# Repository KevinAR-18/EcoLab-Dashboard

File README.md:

# EcoLab Dashboard - Smart Laboratory Management System

EcoLab Dashboard - DTEDI Electronics Laboratory Internship 2025 x Final Project  
**Author:** Stephanus Kevin Andika Rata  
**Internship Hardware (Smart AC & Lamp):** Ilham Purnomo

---

## Project Overview

EcoLab Dashboard is a **Smart Laboratory Management System** desktop application built with **PySide6 (Qt)** and **Firebase Authentication** to monitor and control laboratory devices in real time.

The system currently supports:
- **EcoLab Power Monitoring (Growatt)**
- **Smart Socket**
- **Smart Lamp**
- **Smart AC Control**
- **Weather Station Monitoring**
- **Laboratory sensor and device status monitoring**

---

## Main Features

- **Firebase Authentication**: email/password, Google Sign-In, and Guest Mode
- **Role-based Access Control**: guest, user, and admin
- **Session Management**: remember-me support
- **Admin Panel**: laboratory user account management
- **Smart Socket Control**: relay, timer, schedule, and energy monitoring
- **Smart Socket Safety Protection**: load warning, overload popup, and automatic cutoff
- **Smart Socket Power-Off Protection**: admin-configured blocked/password mode with Firebase sync
- **Smart Socket Recording**: store monitoring data in application memory
- **Smart Socket Export**: export per-socket data to CSV
- **Smart Socket Graph**: per-socket monitoring charts inside the control popup
- **EcoLab Power Monitoring**: Growatt inverter monitoring on page 1
- **Weather Station Monitoring**: laboratory weather data monitoring
- **Smart Lamp Control**
- **Smart AC Control**
- **Windows 11 Dark Mode Handling**: light theme enforcement for key widgets

---

## Technology Stack

### Frontend
- **PySide6** (Qt6)
- **Python** 3.10+
- **PySide6.QtCharts** for Smart Socket charts

### Backend / Services
- **Firebase Authentication**
- **Pyrebase4**
- **MQTT** (`paho-mqtt`) for IoT device communication
- **Growatt data integration** for inverter monitoring
- **Weather data integration** for Weather Station monitoring
- **Google Cloud / OAuth config** for Google login

### Hardware
- **Growatt Inverter** for EcoLab Power Monitoring
- **ESP32-C3** for Smart Socket
- **Wemos D1 Mini** for Smart Lamp and Smart AC
- **PZEM-004T v3.0** for Smart Socket energy monitoring
- **DS1302 RTC** for Smart Socket timer and schedule
- **PCB Smart AC & Smart Lamp** designed by **Ilham Purnomo** (KiCad)

---

## Installation

### Prerequisites

```bash
Python 3.10 or higher
```

### Install dependencies

```bash
pip install -r requirements.txt
```

### Runtime configuration

The application needs four external setup areas:

1. Firebase web configuration in `.env`
2. Google OAuth client credential in `credentials/client_secret.json`
3. MQTT TLS certificate in `credentials/ca.crt` or `credentials/ca2.crt`
4. Growatt account credential in `.env`

See [credentials/README.md](credentials/README.md) for the detailed credential guide.

### Firebase setup

1. Create or open the EcoLab project in Firebase Console.
2. Enable Authentication for Email/Password.
3. Enable Google Sign-In in Firebase Authentication if you want Google login.
4. Copy the Firebase web app values into the root `.env` file.
5. Generate a service account key and place it in `credentials/firebase_service_account.json`.

Example Firebase web config values:

```json
{
  "apiKey": "YOUR_API_KEY",
  "authDomain": "YOUR_PROJECT.firebaseapp.com",
  "databaseURL": "https://YOUR_PROJECT.firebaseio.com",
  "projectId": "YOUR_PROJECT_ID",
  "storageBucket": "YOUR_PROJECT.appspot.com",
  "messagingSenderId": "YOUR_SENDER_ID",
  "appId": "YOUR_APP_ID"
}
```

Required `.env` keys:

```env
ECOLAB_FIREBASE_API_KEY=
ECOLAB_FIREBASE_AUTH_DOMAIN=
ECOLAB_FIREBASE_DATABASE_URL=
ECOLAB_FIREBASE_PROJECT_ID=
ECOLAB_FIREBASE_STORAGE_BUCKET=
ECOLAB_FIREBASE_MESSAGING_SENDER_ID=
ECOLAB_FIREBASE_APP_ID=
ECOLAB_FIREBASE_SERVICE_ACCOUNT=
```

Notes:

- Leave `ECOLAB_FIREBASE_SERVICE_ACCOUNT` empty if you use `credentials/firebase_service_account.json`.
- Fill `ECOLAB_FIREBASE_SERVICE_ACCOUNT` only if the service account file is stored somewhere else.

### Google OAuth setup

Google Sign-In does not use only Firebase settings. It also needs a Google OAuth client JSON file.

Prepare:

- `credentials/client_secret.json`

Steps:

1. Open Google Cloud Console.
2. Select the same Google Cloud project linked to EcoLab.
3. Go to `APIs & Services` -> `Credentials`.
4. Create or open the OAuth client used by the app.
5. Download the client JSON.
6. Rename it to `client_secret.json`.
7. Place it inside the `credentials/` folder.

If Google Sign-In fails, the first thing to verify is whether `credentials/client_secret.json` matches the active Google Cloud project.

### MQTT TLS setup

MQTT communication for the IoT devices uses TLS and requires a CA certificate file.

Prepare:

- `credentials/ca.crt` as the default CA certificate
- `credentials/ca2.crt` as an optional backup CA certificate for some simulator or broker setups

Required `.env` keys:

```env
ECOLAB_MQTT_BROKER=
ECOLAB_MQTT_PORT=8883
ECOLAB_MQTT_USERNAME=
ECOLAB_MQTT_PASSWORD=
ECOLAB_MQTT_CA_CERT=credentials/ca.crt
ECOLAB_MQTT_USE_TLS=true
```

What to prepare for MQTT TLS:

1. MQTT broker hostname or IP
2. MQTT username and password
3. TLS-enabled MQTT port, usually `8883`
4. CA certificate file, usually `credentials/ca.crt`
5. Fallback CA certificate if your simulator or broker setup uses `ca2.crt`

Notes:

- `main.py` defaults to `credentials/ca.crt` when `ECOLAB_MQTT_CA_CERT` is not overridden.
- Some simulator files in `hardware_TA/` still point to `ca2.crt`, so keep both certificate files available unless you are standardizing them.
- Do not embed certificate contents directly into the firmware.

### Growatt setup

Dashboard startup currently initializes the Growatt panel during `MainWindow` creation, so these `.env` keys are required when opening the dashboard:

```env
ECOLAB_GROWATT_USERNAME=
ECOLAB_GROWATT_PASSWORD=
```

Notes:

- Use the same Growatt account that has access to the target storage/inverter plant.
- If the account has no accessible plant or storage device, the Growatt panel will fail during startup.

### Minimum files checklist

Before running the app, make sure these files exist:

```text
.env
credentials/client_secret.json
credentials/firebase_service_account.json
credentials/ca.crt
```

Optional but recommended:

```text
credentials/ca2.crt
```

Minimum required `.env` groups for a full dashboard launch:

- Firebase web config keys
- MQTT connection keys
- Growatt account keys

---

## Usage

### Run the application

```bash
python launcher.py
```

### Authentication options

1. **Email Login**  
   Sign in with email and password.
2. **Google Sign-In**  
   Sign in with a Google account.
3. **Guest Mode**  
   Read-only access without device control.

### User roles

| Role | Access |
|------|--------|
| **Guest** | Monitoring only, without device control |
| **User** | Device control and main dashboard access |
| **Admin** | All user features plus the admin panel |

---

## Smart Socket Updates

The current Smart Socket feature set includes:

- Per-socket relay ON/OFF control
- Per-socket timer
- Start/stop schedules with **daily** and **onetime** modes
- Monitoring for **Voltage, Current, Power, Energy, Frequency, PF**
- Control popup with **Control**, **Data**, **Graph**, **Warning**, and **Setting** tabs
- Per-socket monitoring data recording
- Configurable recording interval from the popup
- **Follow Schedule** option to automatically start recording when a schedule becomes active
- **Autosave CSV** when schedule-based recording ends
- Load warning levels for **elevated**, **high**, and **critical** current
- Light warning popup for elevated load with cooldown control
- Critical overload protection with user response popup, grace period, and automatic relay cutoff
- Automatic schedule clearing before forced OFF when overload protection is triggered during an active schedule
- Admin-only Smart Socket **Setting** tab inside the popup to configure power-off protection per socket
- Power-off protection modes: **Blocked** and **Password required**
- Protection configuration stored in **Firebase Realtime Database** so it can be shared across multiple PCs
- Per-socket CSV export
- Per-socket charts with selectable metrics
- Table and chart refresh only while recording is active

Implementation notes:
- The Python Smart Socket simulator has been aligned with the latest firmware concept.
- Firmware files from `smartsocket2.ino` to `smartsocket5.ino` were derived from `smartsocket.ino` with adjusted MQTT topics.

---

## Project Structure

The current project structure after refactoring is:

```text
Aplikasi EcoLab -  New/
|-- launcher.py
|-- loginmain.py
|-- main.py
|-- create_admin.py
|-- README.md
|-- requirements.txt
|-- build.bat
|-- .env.example
|-- auth/
|   |-- auth_service.py
|   `-- session_manager.py
|-- config/
|   |-- firebase_settings.py
|   |-- login_settings.py
|   `-- path_utils.py
|-- dialogs/
|   |-- admin_window.py
|   `-- smartsocket_popup.py
|-- services/
|   |-- smartsocket_recorder.py
|   |-- smartsocket_protection_store.py
|   `-- smartsocket_settings_manager.py
|-- app/
|   `-- setup/
|       |-- ac_setup.py
|       |-- arrow_setup.py
|       |-- lamp_setup.py
|       |-- smartsocket_setup.py
|       `-- switch_setup.py
|-- backend/
|   |-- mqtt_client.py
|   |-- mqtt_dht22_backend.py
|   |-- mcu_status_backend.py
|   |-- smartsocket_backend.py
|   |-- lampbutton_backend.py
|   |-- acbutton_backend.py
|   |-- growatt_backend.py
|   |-- growatt_worker.py
|   `-- weathercloud_backend.py
|-- widgets/
|   |-- ac_button.py
|   |-- flow_arrow.py
|   |-- lamp_button.py
|   `-- switch_button.py
|-- ui/
|   |   (Qt Designer .ui source files)
|   |-- ui_functions.py
|   |-- ui_theme_helper.py
|   |-- ui_loginpage.py
|   |-- ui_mainwindow.py
|   |-- ui_adminpanel.py
|   |-- ui_role_selection.py
|   `-- ui_smartsocket_popup.py
|-- credentials/
|-- icon/
|-- images/
|-- hardware_TA/
|   `-- PCB Designs/            (KiCad PCB layouts by Ilham Purnomo)
`-- resources_rc.py
```

---

## Architecture Overview

### Entry Flow

- `launcher.py` is the main application entry point.
- It loads any saved session through `auth/session_manager.py`.
- If a valid session exists, it opens the main dashboard.
- Otherwise, it opens `loginmain.py`.

### Authentication Layer

- `auth/auth_service.py` handles Firebase authentication and user records.
- `auth/session_manager.py` stores the local session file used by remember-me behavior.
- `create_admin.py` is a helper script for manually creating the first admin account.

### Main Application Layer

- `main.py` contains the main dashboard window and top-level application orchestration.
- `loginmain.py` handles login, sign-up, forgot password, guest mode, and the admin/dashboard selection flow.
- `dialogs/admin_window.py` contains the admin panel.
- `dialogs/smartsocket_popup.py` contains the detailed Smart Socket control and monitoring popup.
- `services/smartsocket_protection_store.py` stores Smart Socket power-off protection data in Firebase Realtime Database.

### Setup Helpers

The `app/setup/` modules are thin UI wiring helpers:

- `lamp_setup.py` creates and connects custom lamp buttons
- `switch_setup.py` creates and connects Smart Socket switch buttons
- `ac_setup.py` creates and connects the custom AC button
- `arrow_setup.py` creates and stores flow arrows
- `smartsocket_setup.py` connects Smart Socket backend signals to the main window

### Backend Layer

The `backend/` folder contains service and integration modules:

- `mqtt_client.py` manages the shared MQTT connection
- `mqtt_dht22_backend.py` stores and filters DHT22 sensor messages
- `mcu_status_backend.py` tracks MCU online/offline state
- `smartsocket_backend.py` handles MQTT topics for all Smart Socket devices
- `lampbutton_backend.py` and `acbutton_backend.py` send control commands
- `growatt_backend.py` fetches inverter data
- `growatt_worker.py` runs Growatt fetches outside the UI thread
- `weathercloud_backend.py` fetches weather station data

### UI and Widget Layer

- `ui/` contains helper code and generated Python modules from Qt Designer `.ui` files
- `widgets/` contains handwritten custom widgets used by the dashboard
- `resources_rc.py` contains the compiled Qt resource bindings

---

## Hardware TA

The `hardware_TA/` folder contains firmware and simulators used for development and device integration testing.

### Arduino / firmware

1. **smartsocket.ino** - Smart Socket 1 firmware based on MQTT
2. **smartsocket2.ino** - Smart Socket 2 firmware based on MQTT
3. **smartsocket3.ino** - Smart Socket 3 firmware based on MQTT
4. **smartsocket4.ino** - Smart Socket 4 firmware based on MQTT
5. **smartsocket5.ino** - Smart Socket 5 firmware based on MQTT
6. **smartlampcontrol.ino** - Smart Lamp firmware
7. **smartaccontrol.ino** - Smart AC Control firmware

### Python simulators

1. **smartsocket_simulator.py** - Smart Socket 1 simulator
2. **smartsocket2_simulator.py** - Smart Socket 2 simulator
3. **smartsocket3_simulator.py** - Smart Socket 3 simulator
4. **smartsocket4_simulator.py** - Smart Socket 4 simulator
5. **smartsocket5_simulator.py** - Smart Socket 5 simulator
6. **mcua_simulator.py** - MCU-A simulator
7. **mcub_simulator.py** - MCU-B simulator

### Example: run a simulator

```bash
cd hardware_TA
python smartsocket_simulator.py
```

### PCB Designs (KiCad)

- **Smart AC & Smart Lamp** — PCB designed by **Ilham Purnomo** during the 2025 internship.

| PCB | Designer | Location | Description |
|-----|----------|----------|-------------|
| **PCB Smart AC** | Ilham Purnomo | `hardware_TA/PCB Designs/Rangkaian Control AC/PCB AC/` | AC control relay, transformer, and XL6009 DC-DC converter |
| **PCB Smart Lamp** | Ilham Purnomo | `hardware_TA/PCB Designs/Rangkaian Control Lampu/PCB_LAMPU/` | Lamp control relay, transformer, and XL6009 DC-DC converter |

Custom KiCad libraries are located under `Libraries for Arduino IDE/` in each project folder.

---

## Feature Details

### Session management

- Save login sessions
- Remember-me support
- Auto-login when the session is still valid
- Application logout

### Admin panel

- View user list
- Approve accounts
- Update user/admin roles
- Block/unblock accounts
- Update passwords for non-Google users
- Delete accounts

### Smart Socket

- Device status monitoring
- Relay control
- Countdown timer
- Automatic scheduling
- Real-time energy monitoring
- Multi-level current warning system
- Automatic overload cutoff for critical current conditions
- Admin-only power-off protection settings inside the Smart Socket popup
- Power-off protection synced through Firebase so the same socket rules can be read from different PCs
- Data recording, CSV export, and charts
- **Final Project** — fully developed by **Stephanus Kevin Andika Rata** (Hardware & Software)

### Smart Lamp

- Laboratory lamp control
- MQTT-based switching
- Supports multiple lamp channels in the control room page
- Developed together with **Ilham Purnomo**
- Hardware PCB design: **Ilham Purnomo**

### Smart AC

- IR-based AC control
- Cooling and fan modes
- Temperature settings
- Developed together with **Ilham Purnomo**
- Hardware PCB design: **Ilham Purnomo**

### EcoLab Power Monitoring

- Displays **Growatt inverter** data on page 1
- EcoLab power summary and live monitoring
- Serves as the main laboratory energy monitoring page

### Weather Station Monitoring

- Displays laboratory weather station data
- Environmental sensor monitoring on the dashboard
- Integrated into the monitoring page for surrounding condition tracking

---

## Authentication Flow

```text
launcher.py -> check session
  |- valid session -> open dashboard
  |- no session -> open login window
       |- email/password -> Firebase -> save session -> dashboard
       |- Google sign-in -> OAuth -> save session -> dashboard
       |- guest mode -> temp session -> dashboard (limited)
```

---

## Notes

- Use `launcher.py` as the main application entry point.
- The local session file is created automatically after a successful login.
- Firebase credential files are not included in the repository.
- Several key widgets are forced into a light theme to avoid text color issues on Windows 11 dark mode.
- Smart Socket MQTT firmware no longer stores the CA certificate contents directly inside the `.ino` files.

---

## Contact

**Stephanus Kevin Andika Rata**  
Software Development & System Integration  
DTEDI Electronics Laboratory Internship 2025  
Final Project - EcoLab Smart Laboratory  
DTEDI Electronics Laboratory  
Universitas Gadjah Mada

Email: [kevinandika18@gmail.com](mailto:kevinandika18@gmail.com)

**Ilham Purnomo**  
Hardware PCB Design (Smart AC & Smart Lamp)  
DTEDI Electronics Laboratory Internship 2025  
DTEDI Electronics Laboratory  
Universitas Gadjah Mada

---

## License & Copyright

Copyright (c) 2026 **Stephanus Kevin Andika Rata**  
PCB Design (Smart AC & Lamp): **Ilham Purnomo**

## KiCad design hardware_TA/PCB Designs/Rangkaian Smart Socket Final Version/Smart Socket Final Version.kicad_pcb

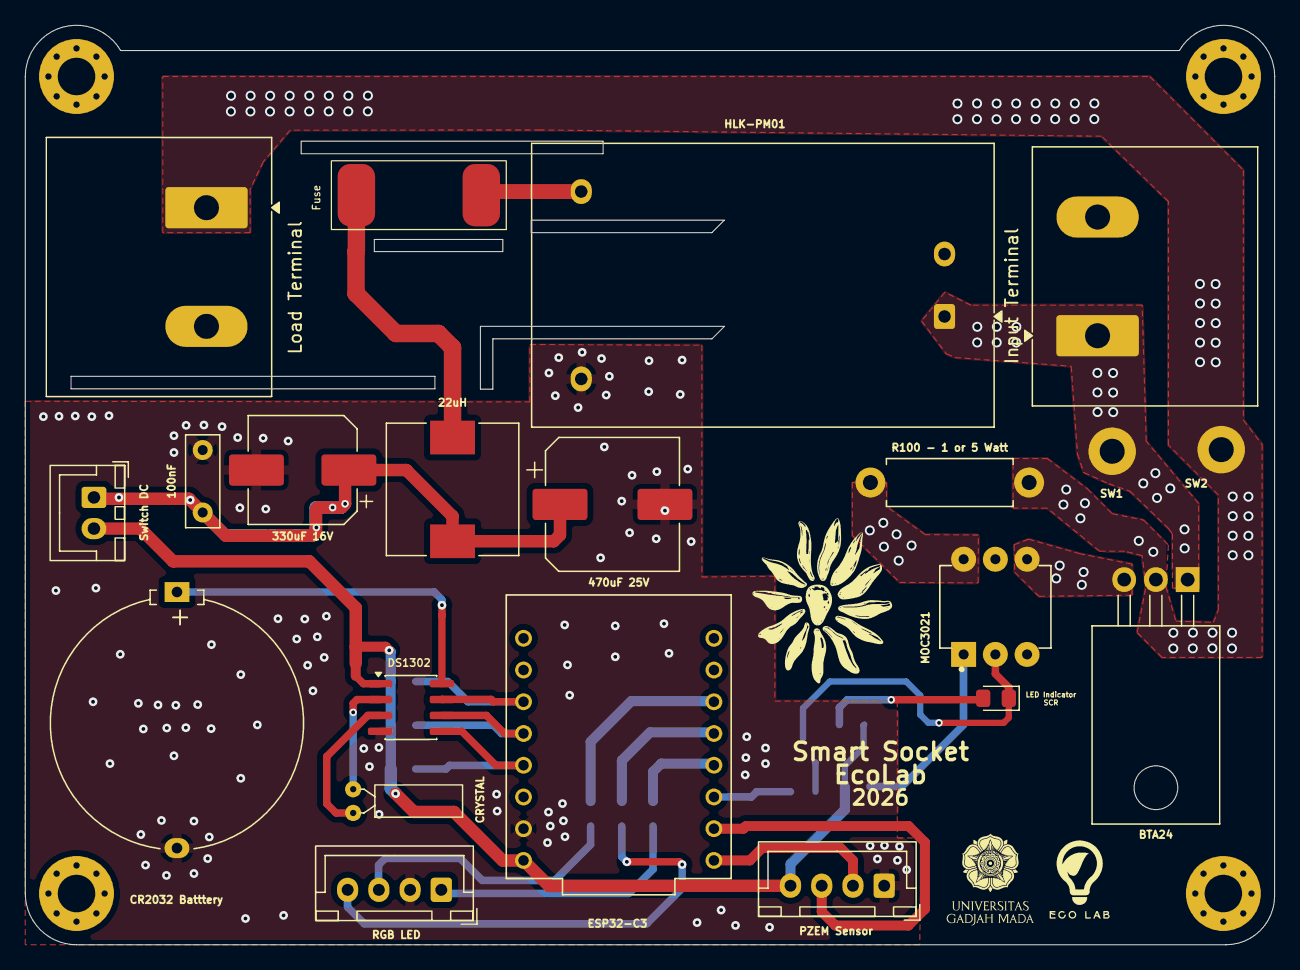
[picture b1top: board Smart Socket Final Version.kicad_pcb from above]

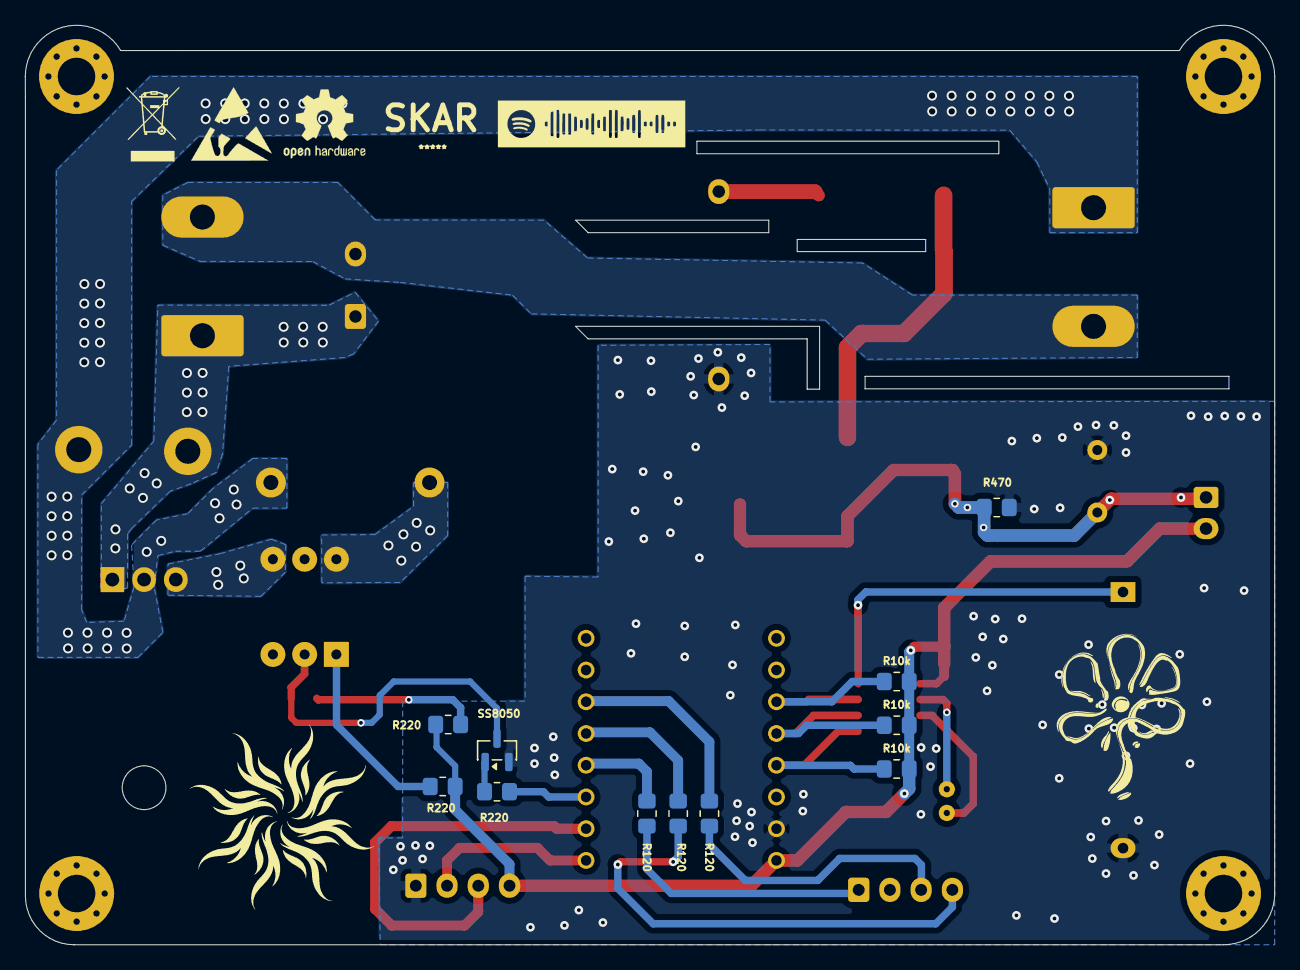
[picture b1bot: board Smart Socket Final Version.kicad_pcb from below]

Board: 2 copper layers, 100.0 x 73.6 mm, 36 parts (11 on the bottom side), 29 nets.

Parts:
22uH: 33uH; L_10.4x10.4_H4.8
100nF: 100nF; C_Rect_L7.2mm_W2.5mm_P5.00mm_FKS2_FKP2_MKS2_MKP2
330uF 16V: 330uF; CP_Elec_8x10.5
470uF 25V: 470uF; CP_Elec_10x10.5
BTA24: BT136-600; TO-220-3_Horizontal_TabDown
CR2032 Batttery: Battery_Cell; Battery_Panasonic_CR2032-HFN_Horizontal_CircularHoles
CRYSTAL: 32.768; Crystal_C26-LF_D2.1mm_L6.5mm_Horizontal
D1: LED; LED_0805_2012Metric_Pad1.15x1.40mm_HandSolder
DS1302: DS1302+; SOIC-8_3.9x4.9mm_P1.27mm
ESP32-C3: ESP32-C3; MODULE_ESP32-C3_SUPERMINI_TH
Fuse: Fuse; Fuse_1808
H3, H4, H5, H6: MountingHole; MountingHole_3mm_Pad_Via
HLK-PM01 : HLK-PM01; Converter_ACDC_Hi-Link_HLK-PMxx
Input Terminal: Input 220V; TerminalBlock_Ningbo-Kagnex_HB9500_1x02_P9.5mm
Load Terminal: AC Socket Load; TerminalBlock_Ningbo-Kagnex_HB9500_1x02_P9.5mm
MOC3021: MOC3021
PZEM Sensor: PZEM Sensor; JST_XH_B4B-XH-A_1x04_P2.50mm_Vertical
R10k, R10k#2, R10k#3: 10k; R_0805_2012Metric_Pad1.20x1.40mm_HandSolder
R100 - 1 or 5 Watt: 100; R_Axial_DIN0411_L9.9mm_D3.6mm_P12.70mm_Horizontal
R120, R120#2, R120#3: 120; R_0805_2012Metric_Pad1.20x1.40mm_HandSolder
R220, R220#2, R220#3: 220; R_0805_2012Metric_Pad1.20x1.40mm_HandSolder
R470: 470; R_0805_2012Metric_Pad1.20x1.40mm_HandSolder
RGB LED: RGB LED; JST_XH_B4B-XH-A_1x04_P2.50mm_Vertical
SS8050: SS8050; SOT-23
SW1: SWITCH FASA IN; MountingHole_2.2mm_M2_DIN965_Pad
SW2: SWITCH FASA to LOAD; MountingHole_2.2mm_M2_DIN965_Pad
Switch DC: DC SWITCH; JST_XH_B2B-XH-A_1x02_P2.50mm_Vertical

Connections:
5V: DS1302.1 (VCC2), ESP32-C3.5V, PZEM Sensor.4, R10k.2, R10k#2.2, R10k#3.2, R220.2, R220#2.2, Switch DC.2
5V Filtered: 22uH.2, 100nF.1, 330uF 16V.1, 470uF 25V.1, R470.2, Switch DC.1
/Fasa to MOC: MOC3021.6, R100 - 1 or 5 Watt.1
/Gate: BTA24.3 (G), MOC3021.4
/VCC1: CR2032 Batttery.1 (+), DS1302.8 (VCC1)
/X1: CRYSTAL.2, DS1302.2 (X1)
/X2: CRYSTAL.1, DS1302.3 (X2)
BLUE LED: ESP32-C3.10 (GPIO10), R120#3.1
CE RTC: DS1302.5 (CE), ESP32-C3.4 (GPIO4), R10k.1
FASA IN: BTA24.1 (A1), HLK-PM01.1 (AC/L), Input Terminal.1, SW1.1
FASA to LOAD: BTA24.2 (A2), Load Terminal.1, R100 - 1 or 5 Watt.2, SW2.1
GND: 100nF.2, 330uF 16V.2, 470uF 25V.2, CR2032 Batttery.2 (-), DS1302.4 (GND), ESP32-C3.G (GND), HLK-PM01.3 (-Vout), PZEM Sensor.1, R470.1, RGB LED.2, SS8050.2 (E)
GREEN LED: ESP32-C3.9 (GPIO9), R120#2.1
IO RTC: DS1302.6 (I/O), ESP32-C3.3 (GPIO3), R10k#3.1
NETRAL: HLK-PM01.2 (AC/N), Input Terminal.2, Load Terminal.2
unnamed: D1.2 (A), R220#2.1
unnamed: D1.1 (K), MOC3021.2, SS8050.3 (C)
unnamed: 22uH.1, Fuse.2
unnamed: R120.2, RGB LED.1
unnamed: R120#3.2, RGB LED.3
unnamed: R120#2.2, RGB LED.4
unnamed: Fuse.1, HLK-PM01.4 (+Vout)
unnamed: R220#3.2, SS8050.1 (B)
unnamed: MOC3021.1, R220.1
RED LED: ESP32-C3.8 (GPIO8), R120.1
RX PZEM: ESP32-C3.6 (GPIO6), PZEM Sensor.3
SCLK RTC: DS1302.7 (SCLK), ESP32-C3.2 (GPIO2), R10k#2.1
TX PZEM: ESP32-C3.5 (GPIO5), PZEM Sensor.2
Trigger SSR: ESP32-C3.7 (GPIO7), R220#3.1

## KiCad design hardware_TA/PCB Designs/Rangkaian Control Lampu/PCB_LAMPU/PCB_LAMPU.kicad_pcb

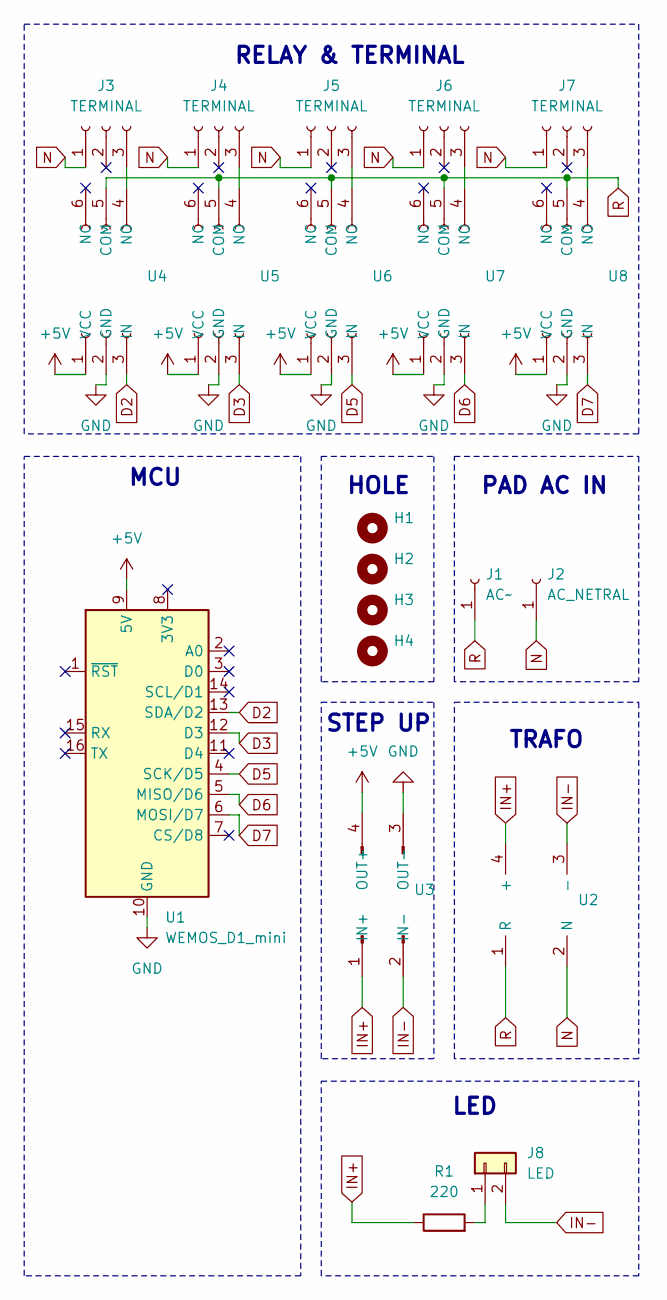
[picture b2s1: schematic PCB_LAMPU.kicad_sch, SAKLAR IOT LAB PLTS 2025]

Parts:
H1, H2, H3, H4: MountingHole; MountingHole_3.2mm_M3_DIN965_Pad
J1: AC~; TestPoint_Pad_4.0x4.0mm
J2: AC_NETRAL; TestPoint_Pad_4.0x4.0mm
J3, J4, J5, J6, J7: TERMINAL; TerminalBlock_MaiXu_MX126-5.0-03P_1x03_P5.00mm
J8: LED; JST_XH_B2B-XH-A_1x02_P2.50mm_Vertical
R1: 220; R_0805_2012Metric
U1: WEMOS_D1_mini; WEMOS_D1_mini_light
U2: TRAFOV1
U3: XL6009_MOD
U4, U5, U6, U7, U8: RELAY_SRD5VDC

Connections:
+5V: U1.9 (5V), U3.4 (OUT+), U4.1 (VCC), U5.1 (VCC), U6.1 (VCC), U7.1 (VCC), U8.1 (VCC)
D2: U1.13 (SDA/D2), U4.3 (IN)
D3: U1.12 (D3), U5.3 (IN)
D5: U1.4 (SCK/D5), U6.3 (IN)
D6: U1.5 (MISO/D6), U7.3 (IN)
D7: U1.6 (MOSI/D7), U8.3 (IN)
GND: U1.10 (GND), U3.3 (OUT-), U4.2 (GND), U5.2 (GND), U6.2 (GND), U7.2 (GND), U8.2 (GND)
IN+: R1.1, U2.4 (+), U3.1 (IN+)
IN-: J8.2, U2.3 (-), U3.2 (IN-)
N: J2.1, J3.1, J4.1, J5.1, J6.1, J7.1, U2.2 (N)
unnamed: J3.3, U4.4 (NO)
unnamed: J4.3, U5.4 (NO)
unnamed: J5.3, U6.4 (NO)
unnamed: J6.3, U7.4 (NO)
unnamed: J7.3, U8.4 (NO)
unnamed: J8.1, R1.2
R: J1.1, U2.1 (R), U4.5 (COM), U5.5 (COM), U6.5 (COM), U7.5 (COM), U8.5 (COM)

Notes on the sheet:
HOLE
PAD AC IN
STEP UP
RELAY & TERMINAL
MCU
LED
TRAFO

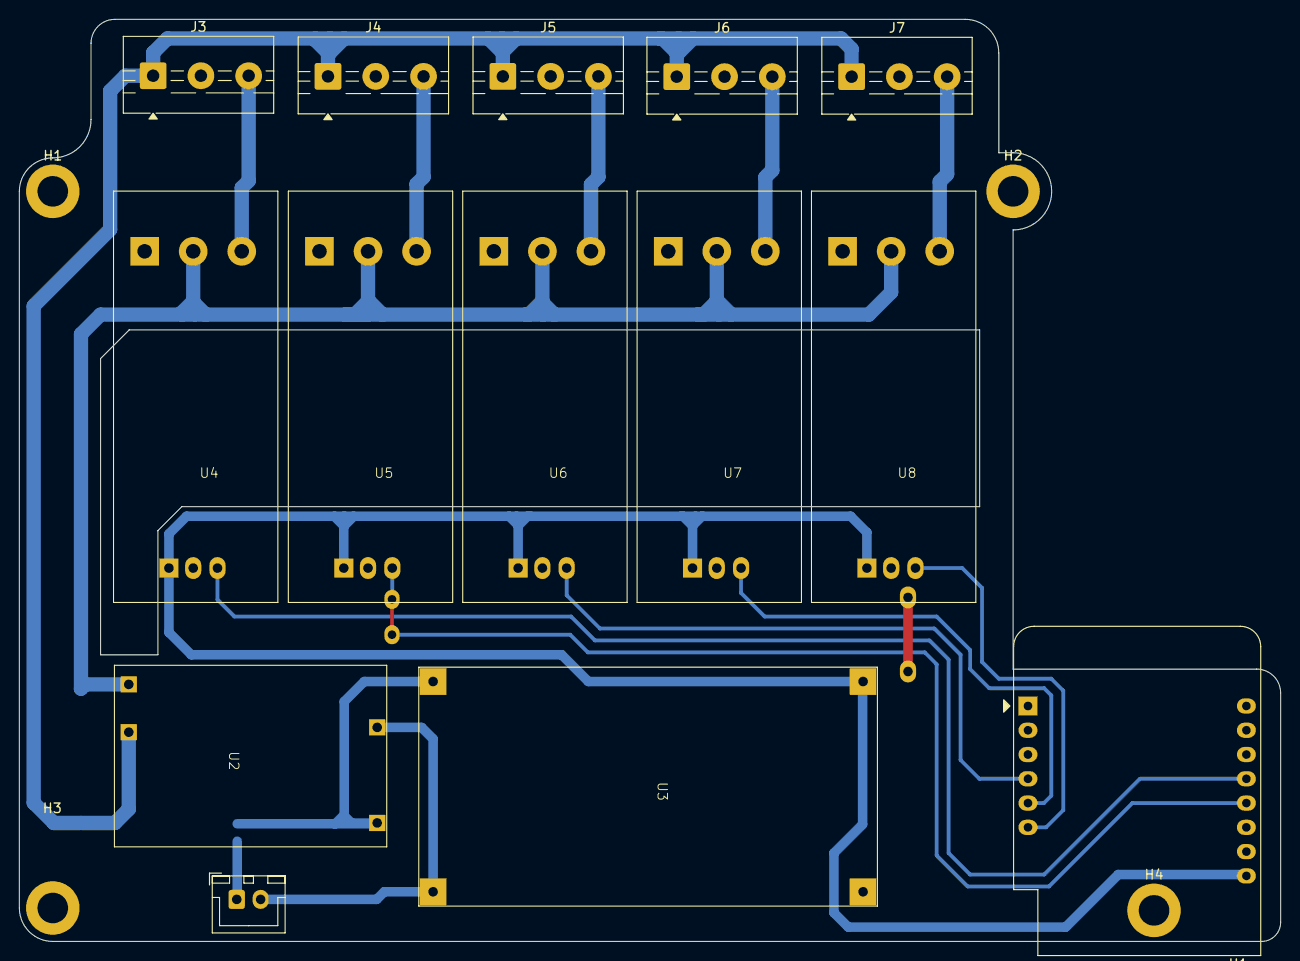
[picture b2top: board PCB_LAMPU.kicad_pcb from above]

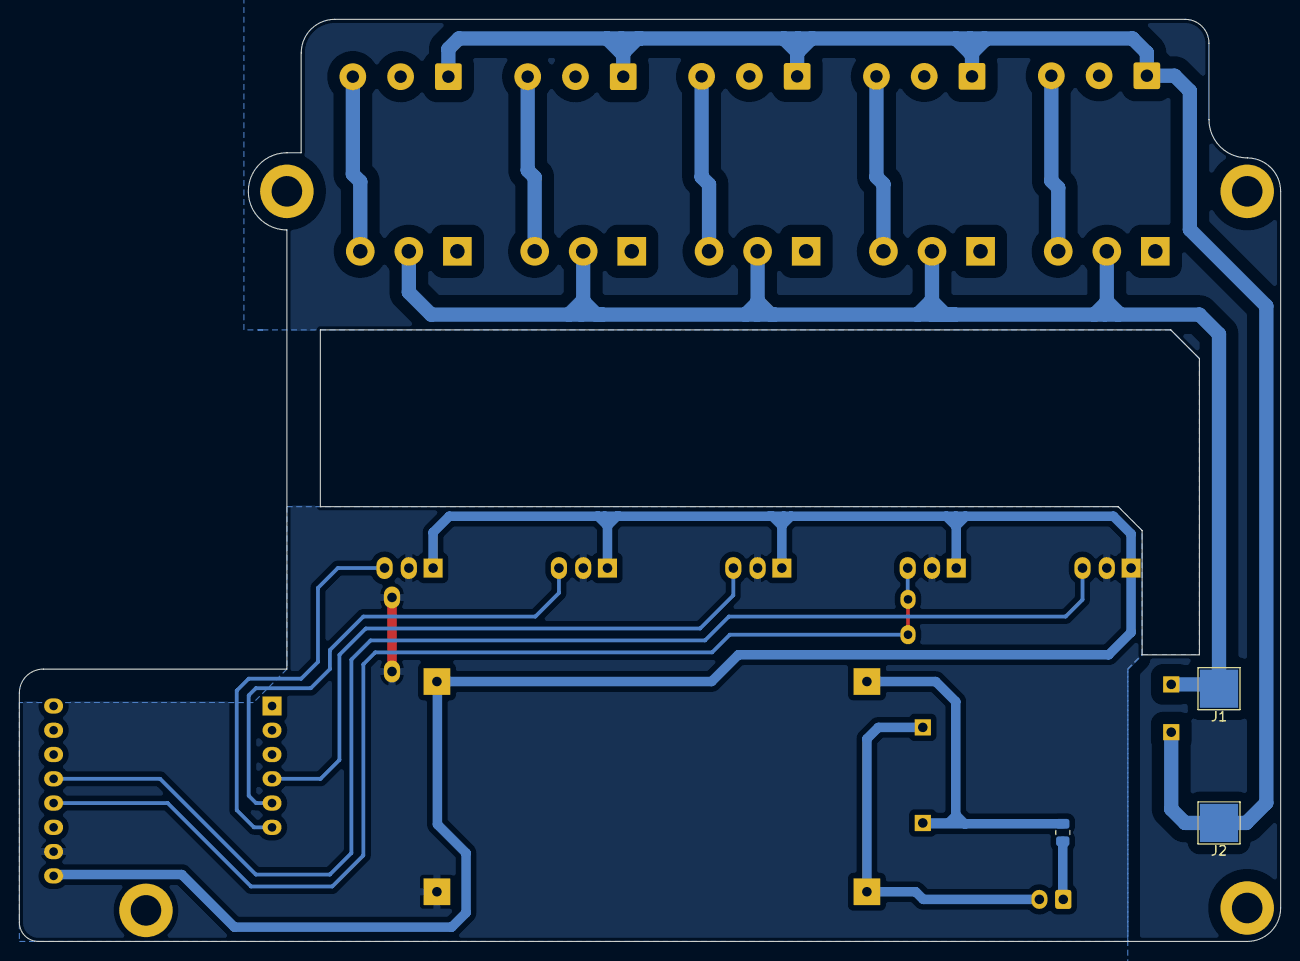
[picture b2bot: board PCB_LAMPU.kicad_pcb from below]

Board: 2 copper layers, 132.0 x 96.5 mm, 21 parts (3 on the bottom side), 17 nets.

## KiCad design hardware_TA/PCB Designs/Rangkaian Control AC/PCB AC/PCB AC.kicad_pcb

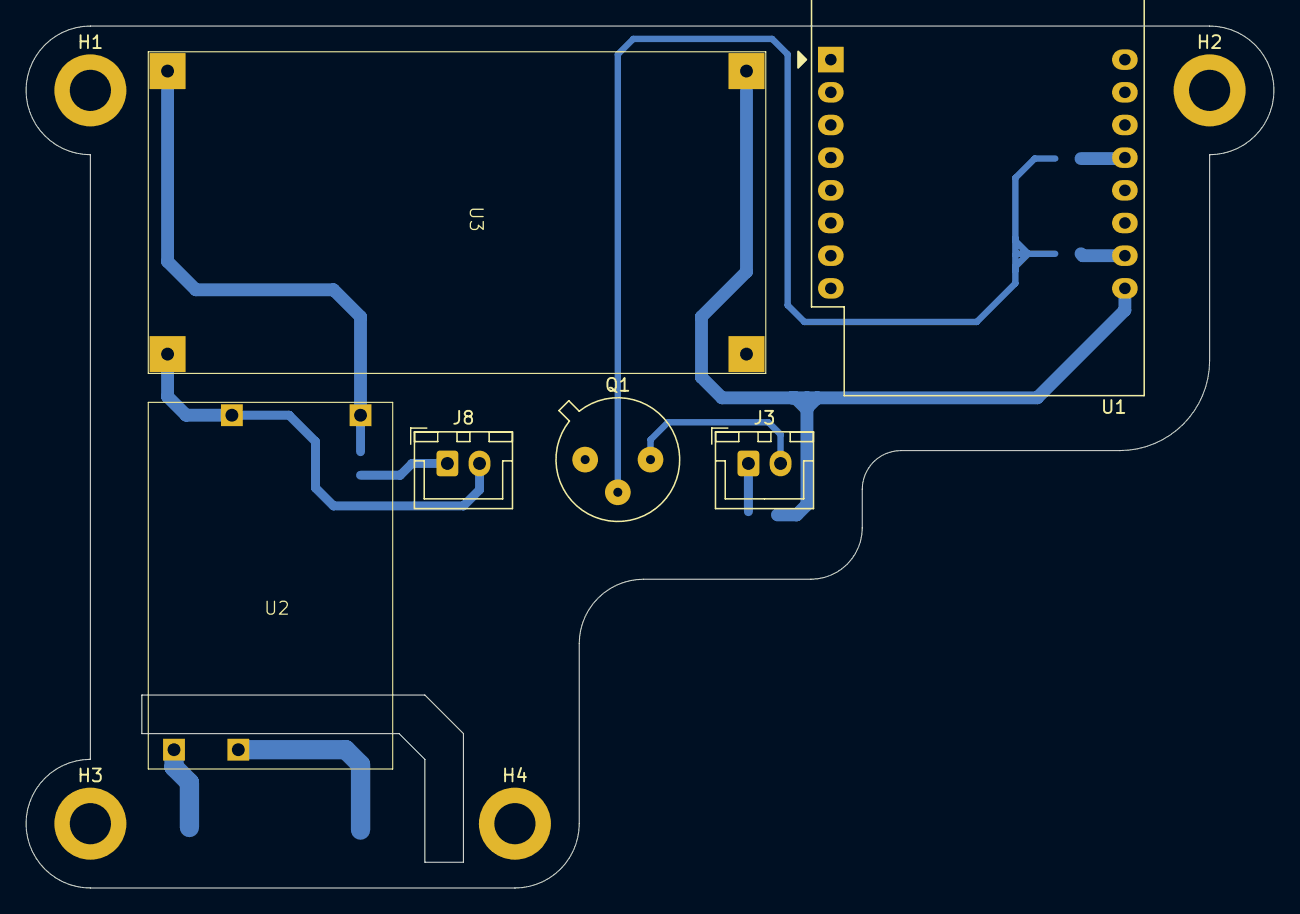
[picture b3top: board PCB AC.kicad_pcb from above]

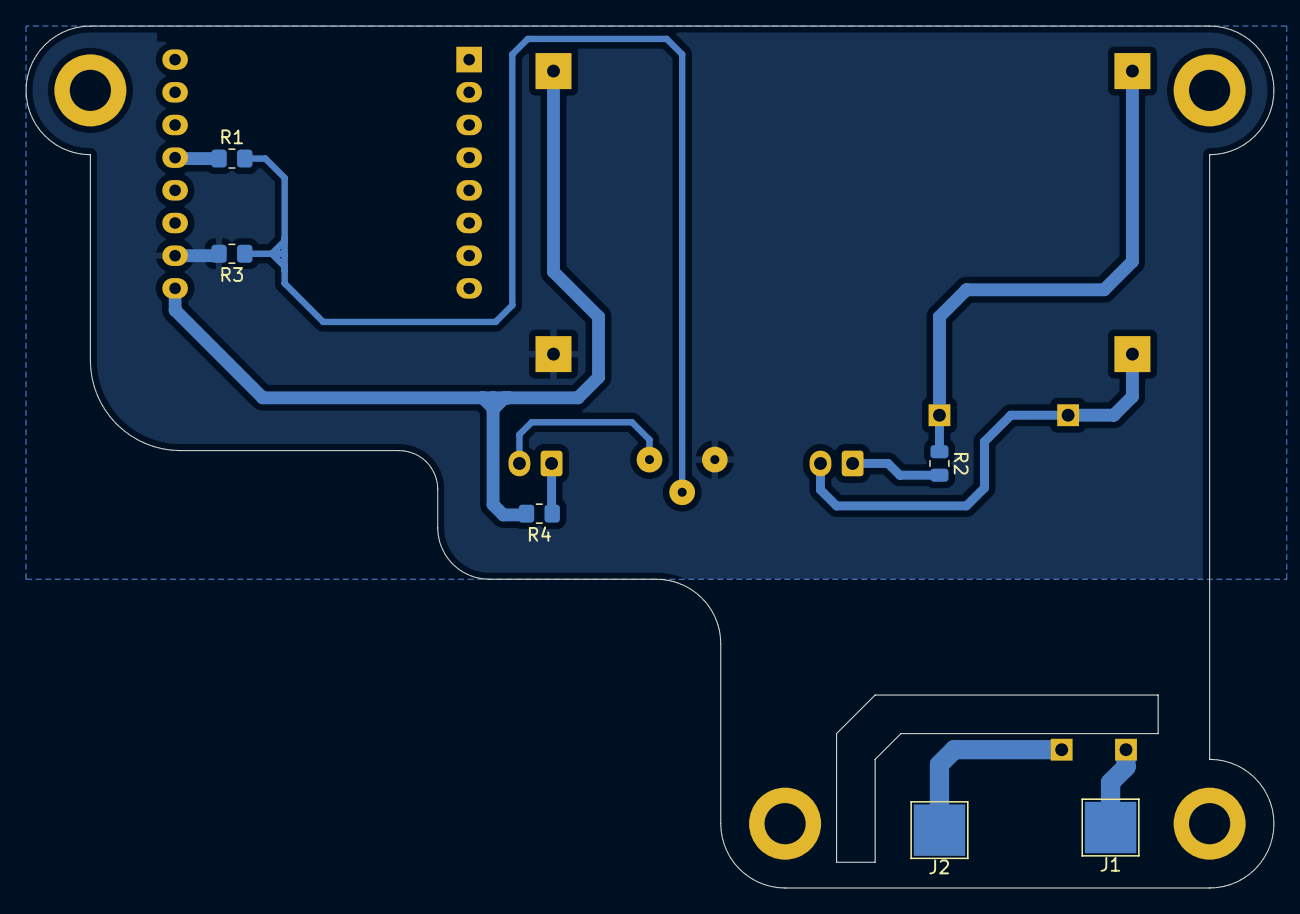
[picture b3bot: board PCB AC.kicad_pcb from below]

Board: 2 copper layers, 97.0 x 67.0 mm, 16 parts (6 on the bottom side), 11 nets.

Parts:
H1, H2, H3, H4: MountingHole; MountingHole_3.2mm_M3_DIN965_Pad
J1: AC~; TestPoint_Pad_4.0x4.0mm
J2: AC_NETRAL; TestPoint_Pad_4.0x4.0mm
J3: IR; JST_XH_B2B-XH-A_1x02_P2.50mm_Vertical
J8: LED; JST_XH_B2B-XH-A_1x02_P2.50mm_Vertical
Q1: 2N2219; TO-39-3
R1, R4: 100; R_0805_2012Metric_Pad1.20x1.40mm_HandSolder
R2: 220; R_0805_2012Metric
R3: 10k; R_0805_2012Metric_Pad1.20x1.40mm_HandSolder
U1: WEMOS_D1_mini; WEMOS_D1_mini_light
U2: TRAFOV1
U3: XL6009_MOD

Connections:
+5V: R4.2, U1.9 (5V), U3.4 (OUT+)
D2: R1.1, U1.13 (SDA/D2)
GND: Q1.1 (E), R3.2, U1.10 (GND), U3.3 (OUT-)
IN+: R2.1, U2.4 (+), U3.1 (IN+)
IN-: J8.2, U2.3 (-), U3.2 (IN-)
N: J2.1, U2.2 (N)
unnamed: J3.1, R4.1
unnamed: J3.2, Q1.3 (C)
unnamed: J8.1, R2.2
unnamed: Q1.2 (B), R1.2, R3.1
R: J1.1, U2.1 (R)

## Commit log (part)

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2025-10-21 New File
2025-10-21 Initial Files
2025-12-22 Initial commit EcoLab Dashboard
2025-12-22 Add gitignore and clean project
2025-12-22 Comment Update
2025-12-23 update style warna
2025-12-24 big update from lab
2025-12-24 updateicon dan window title
2025-12-25 updateicon dan exe
2025-12-25 updategitignore
2026-02-03 updatesinkron
2026-02-04 updatesetup
2026-03-06 updateprogramhardawarecobacoba
2026-03-09 refactor: modularize trialloginpage auth, settings, and UI pages
2026-03-09 refactor: enhance admin panel and authentication service with user management features
2026-03-09 refactor: update user authentication handling google auth
2026-03-09 feat: - redirect user with role "user" to dashboard ecolab on root folder main.py
2026-03-11 updateuiadminpanel
2026-03-21 - Added `admin_window.py` for the Admin Panel functionality, including user management features such as approving accounts, updating passwords, blocking/unblocking users, and deleting users. - Introd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
2026-03-21 Refactor UI styles for consistency and readability; adjust font sizes and background colors in `ecolab.ui` and `ui_mainwindow.py`
2026-03-21 Implement session management and user authentication features; add SessionManager, update login flow, and enhance user experience with remember me functionality
2026-03-21 Enhance input field styles for better readability; update username and email QLineEdit properties with improved font size, weight, and color.
2026-03-21 Refactor user role and authentication provider checks; enhance button visibility and tooltips for guest and Google users in the main window.
2026-03-22 Rename Growatt graph button and page to Smart Socket for improved functionality and clarity.
2026-03-23 Add signin and signup images
    - Added signin.png to the images directory.
    - Added signup.png to the images directory.
2026-03-23 Add SmartSocketPopup UI and functionality
    - Created a new UI file for SmartSocketPopup with a modern design, including timer and schedule functionalities.
    - Implemented the SmartSocketPopup class in Python, connecting UI elements to their respective handlers.
    - Added functionality for starting and canceling timers, as well as setting and clearing schedules.
    - Integrated dynamic title updates based on the socket number and improved user feedback through status labels.
    - Ensured the dialog can be dragged by implementing mouse event handlers for a borderless window experience.
2026-03-24 Remove unused image files SS1.jpg and ss2.jpg to declutter the project.
2026-03-24 Add application version management; display version in the UI
2026-03-24 feat: Implement real-time lamp control and DHT sensor updates via MQTT
    - Added signal emission for lamp status changes in LampButtonBackend.
    - Enhanced DHT22MQTTBackend to validate sensor data and handle data expiry.
    - Updated MainWindow to connect new signals for lamp and AC status changes.
    - Created DHT info popup for displaying sensor data in the UI.
    - Developed MCU A and B simulators for testing lamp and AC control with DHT sensor data.
    - Migrated MQTT communication to use TLS for secure connections.
2026-03-25 feat: Add EcoLab Smart Socket Simulator and SmartSocket Setup UI
    - Implemented the EcoLab Smart Socket Simulator with MQTT functionalities, including relay control, timer, and scheduling features.
    - Added realistic energy monitoring simulation with adjustable load current.
    - Created SmartSocket Setup class to manage UI connections for multiple sockets, ensuring real-time updates on status and energy data.
2026-03-25 feat: Prevent multiple Smart Socket popups from opening
2026-03-25 feat: Add RTC functionality with DS1302 library for time management
2026-03-26 feat: Enhance user interface and accessibility for admin panel and device controls
2026-03-26 feat: Enhance login functionality with Enter key support and custom message box handling
2026-03-26 fix: Update notes for admin panel and smart socket to improve clarity and consistency
2026-03-26 fix: Update application version from v2.0-beta to v2.0
2026-03-26 fix: Prevent Dark Mode interference by forcing label colors in Admin Panel
2026-03-26 updatenotelagi
2026-03-26 feat: Enhance message box styling to prevent Dark Mode interference
2026-03-26 updatenotelagii
2026-03-26 HOREEE BERHASILL
2026-03-29 feat: Add session management enhancements and cleanup on app quit
2026-03-30 feat: Add Smart AC and Lamp control functionality with MQTT and DHT sensor integration
2026-04-01 test update
2026-04-01 feat: Update MQTT configuration to use insecure TLS mode and add technical explanation for CA certificate limitations
2026-04-03 feat: Add credential setup documentation for Firebase and Google Cloud
2026-04-03 refactor: Update .gitignore to better organize credential files and remove unnecessary entries
2026-04-03 refactor: Remove debug print statements from switch toggle handler
2026-04-03 docs: Update README.md with comprehensive project overview, features, tech stack, installation instructions, and usage details
2026-04-03 updatelagi
2026-04-03 docs: Update hardware section in README.md to specify microcontrollers for lab equipment
2026-04-03 docs: Update license section in README.md to include copyright and usage terms
2026-04-03 updatereadmeagainnn
2026-04-06 Update settinng build exe
2026-04-06 update tampilan gui growatt
2026-04-06 updatefileinstalforge
2026-04-07 updatesessionmanager
2026-04-12 add DOKUMENTASI_ECOLAB.txt to .gitignore
2026-04-19 add debugpcb.ino for RTC and PZEM integration with relay control
2026-04-20 Fix smart socket offline behavior and remove RTC popup
2026-04-23 Add SmartSocket5 firmware with WiFi, MQTT, RTC, and scheduling features
2026-04-25 Refactor Smart Socket Code and Enhance Monitoring Features
    - Updated pin definitions for LED colors in smartsocket5.ino.
    - Added TLS certificate directly in smartsocket5.ino for secure MQTT connection.
    - Modified smartsocket_simulator.py to reflect firmware-like behavior for energy monitoring.
    - Enhanced MQTT connection handling and added error handling in smartsocket_simulator.py.
    - Introduced SmartSocketRecorder class for recording energy data and managing socket states.
    - Integrated recording functionality into the main application, allowing for start/stop recording and CSV export.
2026-04-26 Refactor UI components and enhance Smart Socket functionality
    - Integrated theme helper functions for consistent UI styling across LoginWindow and SmartSocketPopup.
    - Replaced QMessageBox with styled functions for better visual consistency in LoginWindow.
    - Added socket recording state change signals in MainWindow to improve interactivity with SmartSocketPopup.
    - Implemented autosave feature for Smart Socket recordings, allowing users to specify a directory for automatic CSV exports.
    - Introduced adjustable recording intervals for Smart Socket data collection, enhancing user control over data sampling rates.
    - Updated schedule configuration in JSON to change default start hour for better usa
2026-04-26 Update MQTT CA certificate path and comment out temporary drag background functionality
2026-04-26 Refactor README.md for improved clarity and organization of project features and tech stack
2026-04-29 feat: Enhance SmartSocket functionality with custom graph range and data handling
    - Added logic to handle cases where current value is less than 0.1 in main.py, setting power, pf, and energy to 0.
    - Updated energy recording to use modified display data in main.py.
    - Introduced custom Y-axis range controls in SmartSocketPopup, allowing users to set min and max values for graphs.
    - Implemented validation for custom range inputs and added apply/reset functionality in SmartSocketPopup.
    - Enhanced graph rendering logic to respect custom ranges and display appropriate status messages.
    - Created a new JSON configuration file (schedule_socket2.json) for socket scheduling settings.
2026-05-03 chore: Comment out temporary drag background functionality in main window
2026-05-03 feat: Update build script for PyInstaller compatibility and enhance hidden-imports
2026-05-04 feat: Update MQTT broker and CA certificate paths in simulator scripts
2026-05-06 Remove the generated UI code for the login page to streamline the project structure and avoid conflicts during UI recompilation.
2026-05-06 chore: remove obsolete configuration files and scripts to clean up the project
2026-05-06 feat: update Firebase authentication service and configuration management
2026-05-06 feat: enhance environment configuration and update Growatt backend authentication
2026-05-06 Refactor and enhance UI components and backend services
    - Updated ArrowSetup to improve documentation and centralize arrow references.
    - Enhanced LampSetup with clearer comments and tooltip descriptions.
    - Simplified SmartSocketSetup by using a loop for signal connections, reducing redundancy.
    - Improved SwitchSetup documentation for clarity on widget creation and signal connections.
    - Added detailed docstrings to FirebaseAuthAdminClient and FirebaseAuthService for better understanding of their roles.
    - Streamlined SessionManager methods, enhancing readability and error handling.
2026-05-06 docs: update README.md for project structure and architecture overview in Indonesian
2026-05-06 docs: update README.md to translate sections into Indonesian and improve clarity
2026-05-06 docs: update README.md for improved clarity and consistency in English and Indonesian sections
2026-05-06 docs: update README.md and remove outdated credential setup files
2026-05-07 feat: enhance socket warning system with critical load handling and popup notifications
2026-05-07 feat: optimize MCU status handling and improve UI update efficiency
2026-05-07 feat: improve UI responsiveness and streamline sensor panel updates
2026-05-08 feat: update .gitignore to include setup files and remove mouse event bindings in main.py
2026-05-08 feat: update .gitignore to exclude EcoLabSetup.exe and include .exe files
2026-05-12 feat: add Smart Socket power-off protection feature with admin configuration
    - Introduced a new feature for Smart Socket that allows power-off protection
    with options for blocked mode and password requirement, synced with Firebase.
    - Updated README.md to include details about the new feature and its setup.
    - Enhanced the MQTT client to prevent duplicate subscriptions.
    - Refactored SmartSocketManager to remove initial status requests for devices.
    - Improved the UI for SmartSocketPopup to include a new settings tab for power-off protection.
2026-05-12 feat: update app version to v2.1
2026-05-12 feat: add EcoLabSetup.exe to .gitignore for proper file handling
2026-05-13 feat: add EcoLabSetup.exe to .gitignore to prevent tracking of setup file
2026-05-23 feat: update logging functionality and configuration for MQTT client and Smart Socket
2026-05-24 feat: enhance styling for mqttLogModeCombo in MainWindow
2026-05-24 fix: update copyright year and clarify project usage terms in README
2026-05-27 feat: update MQTT credentials to use environment variables for security
2026-05-29 refactor: streamline PyInstaller build by removing unused hidden imports and adding exclusions
2026-06-01 feat: update Smart Socket control logic to restrict user actions based on active timers and schedules; add release notes for v2.1.3
2026-06-23 feat: update Smart Socket timer controls to disable for regular users when schedule is active; bump version to v2.1.4 and add release notes
2026-06-23 feat: update SmartSocketPopup to manage schedule status changes and enhance timer controls; bump version to v2.1.4
2026-06-23 feat: update SmartSocketPopup to enhance timer control tooltips and improve user feedback for active schedules
2026-06-23 feat: update admin role management to use superior admin emails and enhance role change restrictions
2026-06-23 feat: update MQTT configuration for smartsocket simulators with new broker and credentials
2026-06-23 feat: add comments to all py files
